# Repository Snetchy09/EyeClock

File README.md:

here is the EyeClock , it a clock that has time and eyes that move , Blare Hack Club 

Challenges:
i have never made a hardware project before , i have never used Kicad and onshape , the hardet part for me was making the CAD , due to poor 3d movement support in mu laptop , and the fact the clock is tilted and i took so long trying to fit the screen and the pcb inside the case

Inspiration:
i took inspiration from a toy i had as a kid wich had small cool eyes that move and follow the user , tho the clock i made doesnt have camera nor sensors so the eyes movment is random

BOM:
1x Seeed XIAO ESP32 C3
1x ST7789 2.25 in TFT screen
1x buzzer
3x Cherry MX Switches
3x Blank DSA Keycaps
8x M3x16 Bolt

PCB:

Schematic:

Case parts:

case without the top part:

case without the bottom part:

C

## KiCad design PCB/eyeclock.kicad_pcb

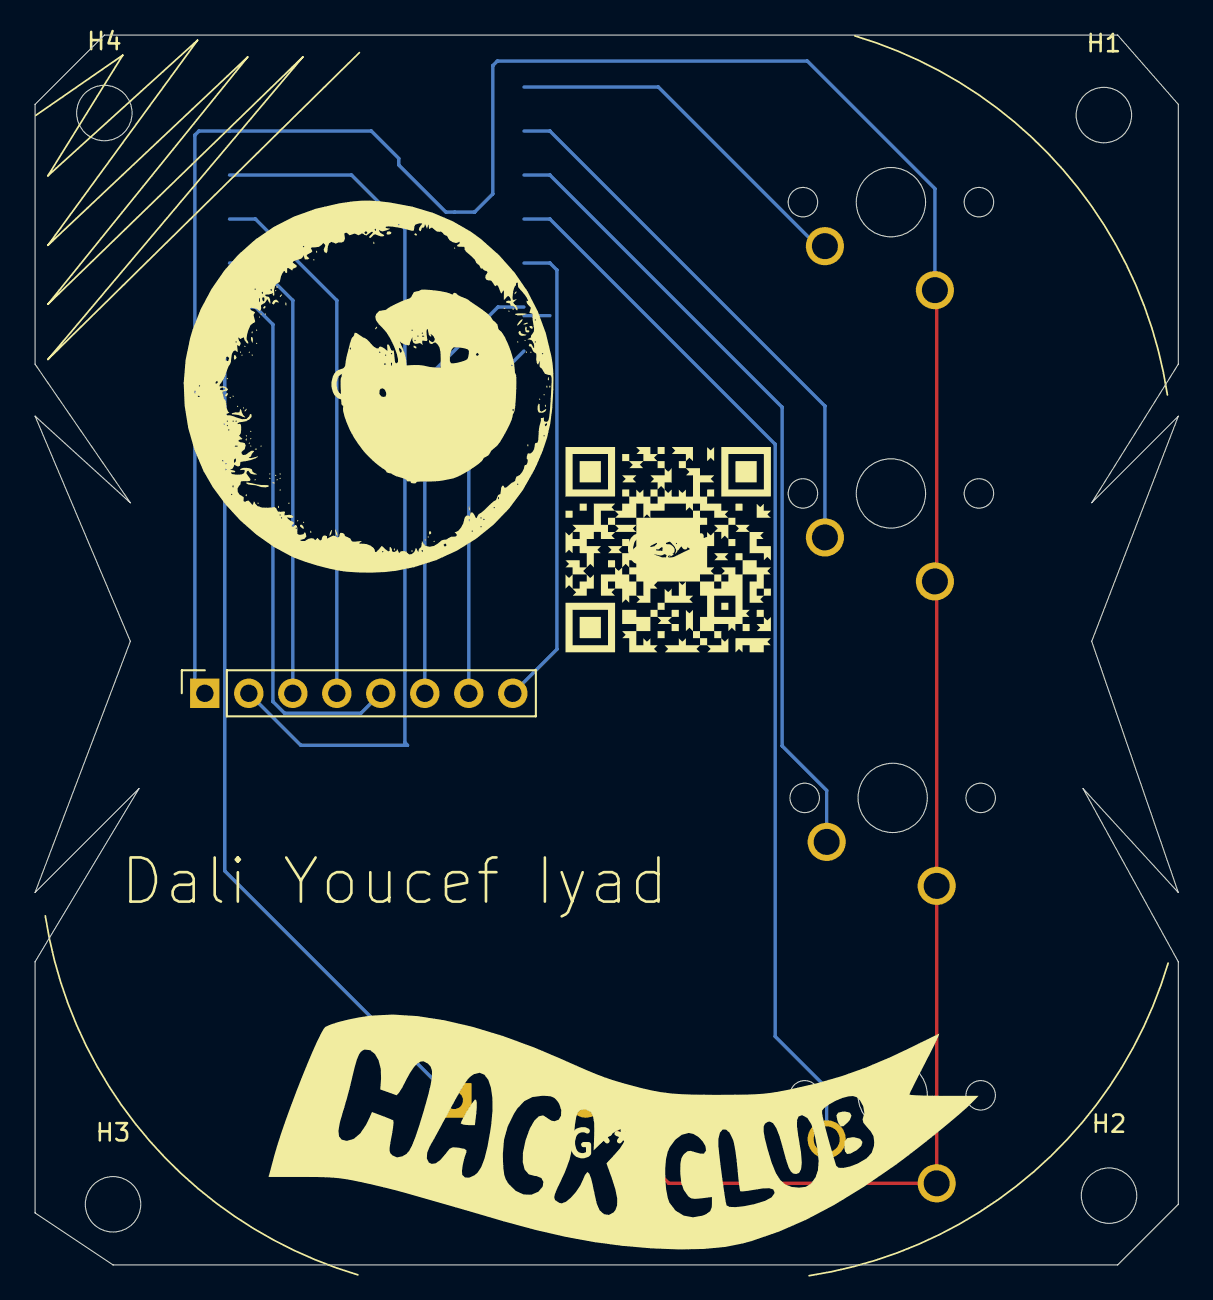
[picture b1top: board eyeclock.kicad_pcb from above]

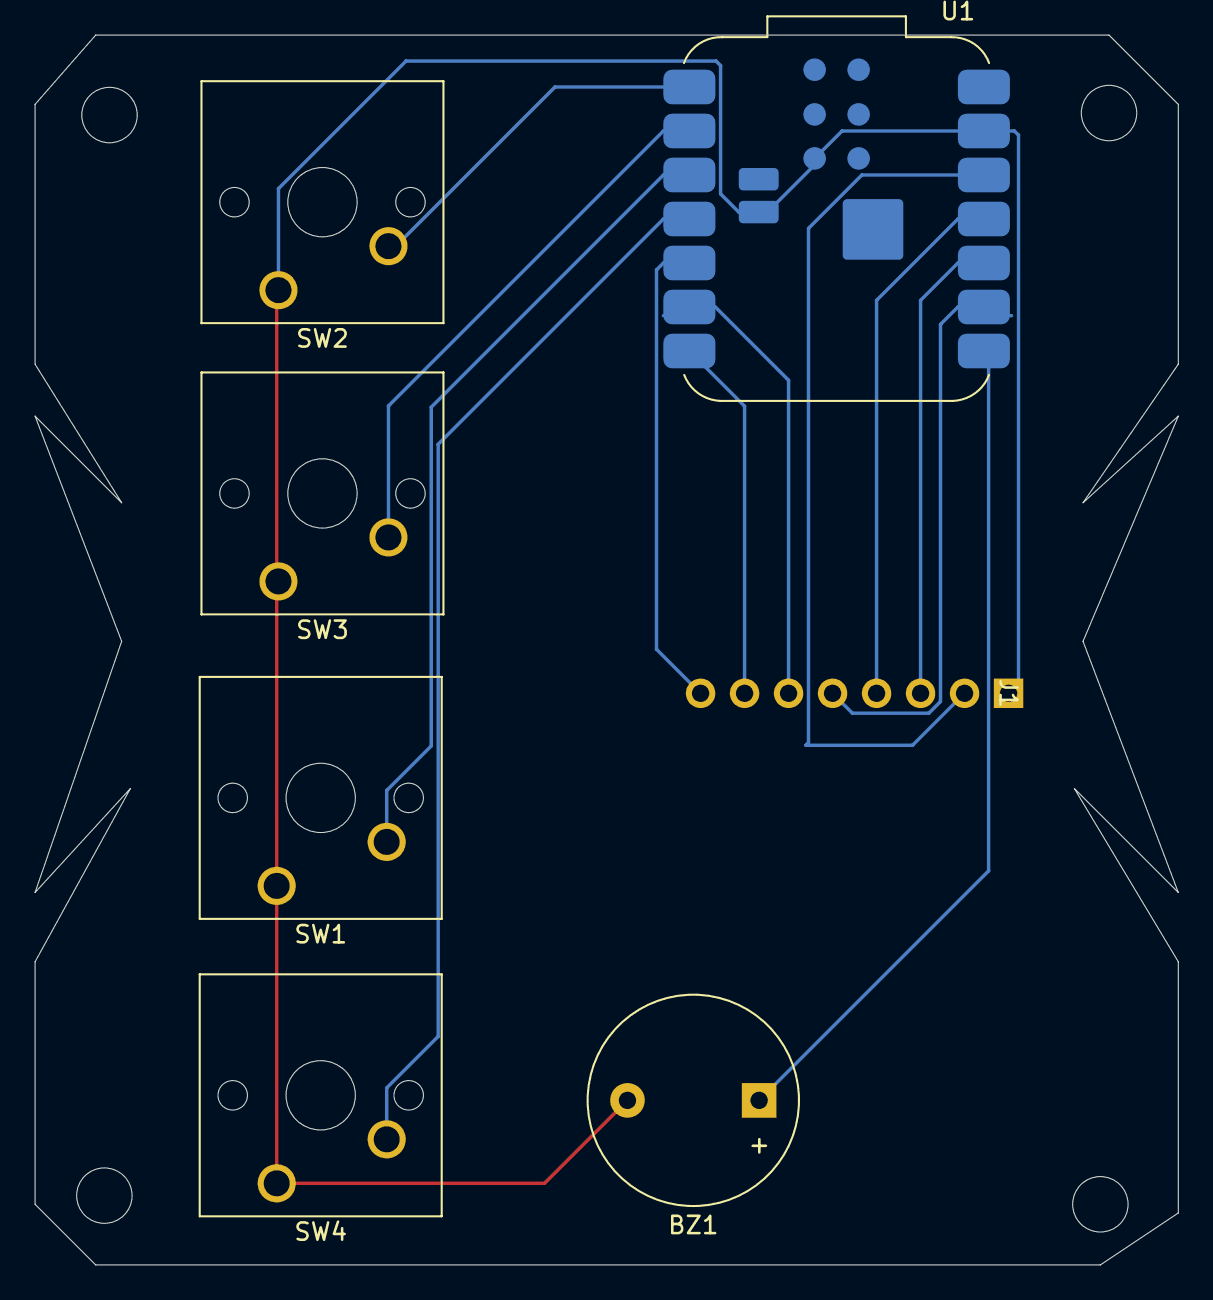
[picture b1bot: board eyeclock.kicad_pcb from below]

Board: 2 copper layers, 66.0 x 71.0 mm, 11 parts (6 on the bottom side), 13 nets.

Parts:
BZ1: Buzzer; Buzzer_12x9.5RM7.6
H1, H2, H3, H4: MountingHole; MountingHole_3.2mm_M3
J1: Conn_01x08_Pin; PinSocket_1x08_P2.54mm_Vertical
SW1, SW2, SW3, SW4: SW_Push; SW_Cherry_MX_1.00u_PCB
U1: XIAO-ESP32-C3-SMD; MCU_Seeed_ESP32C3

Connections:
+3V3: J1.2, U1.12 (3V3)
/BO: J1.7, U1.7 (PB08_A6_D6_TX)
/DO: J1.8, U1.5 (PA8_A4_D4_SDA)
/HO: J1.6, U1.6 (PA9_A5_D5_SCL)
GND: BZ1.2 (-), J1.1, SW1.1, SW2.1, SW3.1, SW4.1, U1.13 (GND), U1.16 (GND), U1.20 (GND)
unnamed: BZ1.1 (+), U1.8 (PB09_A7_D7_RX)
unnamed: J1.3, U1.10 (PA5_A9_D9_MISO)
unnamed: J1.4, U1.11 (PA6_A10_D10_MOSI)
unnamed: J1.5, U1.9 (PA7_A8_D8_SCK)
unnamed: SW2.2, U1.1 (PA02_A0_D0)
unnamed: SW3.2, U1.2 (PA4_A1_D1)
unnamed: SW1.2, U1.3 (PA10_A2_D2)
unnamed: SW4.2, U1.4 (PA11_A3_D3)
